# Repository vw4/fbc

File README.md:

# Footwell Backlight Controller

- Independent two-channel control with smooth fade transitions
- Delayed switch-off feature (can be disabled via T58b input)
- Low power standby mode

### FSM Diagram

## Schematics

## Partlist

### PCB

There are known issues with PCB layout

- The distance between the 4-pin connectors and the mounting holes is shorter by 0.5mm.
- All connectors need to be moved outward by 3.6mm to match the case outline.
- There are errors in the positions of the J1 and J2 labels on the silkscreen; the labels are placed on the solder pads.
- D1 is too close to the J3 connector housing.

| Qty | Value        | Device        | Package          | Parts                            | Description                                             | MF MPN        | OC_FARNELL | OC_NEWARK | PACKAGE  | SUPPLIER        |
|-----|--------------|---------------|------------------|----------------------------------|---------------------------------------------------------|---------------|------------|-----------|----------|-----------------|
| 2   | 100n         | Capacitor     | C025-025X050     | C1, C3                           | ceramic or polyester capacitor                          |               |            |           |          |                 |
| 2   | 100uF 20V    | Capacitor     | E3,5-8           | C2, C4                           | electrolytic capacitor                                  |               |            |           |          |                 |
| 8   | 10k          | Resistor      | 0207/10          | R1, R2, R3, R5, R8, R9, R12, R13 | 1/4 Watt, ±5%                                           |               |            |           |          |                 |
| 1   | 1N4004       | 1N4004        | DO41-10          | D1                               | DIODE                                                   |               |            |           |          |                 |
| 2   | 1N4148       | 1N4148        | DO35-10          | D2, D3                           | DIODE                                                   |               |            |           |          |                 |
| 3   | 1k           | Resistor      | 0207/10          | R4, R10, R11                     | 1/4 Watt, ±5%                                           |               |            |           |          |                 |
| 2   | 2.2k         | Resistor      | 0207/10          | R6, R7                           | 1/4 Watt, ±5%                                           |               |            |           |          |                 |
| 2   | 5-104935-6   | Connector     | 7395-04          | J1, J2                           | CONNECTOR - LATCHING HDR SHRD 5P W/O HOLD-DN 30AU CNT   | 5-104935-6    |            |           |          | TE Connectivity |
| 1   | 5-104935-6   | Connector     | 7395-05          | J3                               | CONNECTOR - LATCHING HDR SHRD 4P W/O HOLD-DN 30AU CNT   | 5-104935-1    |            |           |          | TE Connectivity |
| 1   | 4N25M        | 4N25M         | DIL06            | OK1                              | General Purpose 6-Pin Phototransistor Optocouplers      | 4N25-M        | 1021349    | 98K9084   |          |                 |
| 1   | 78L05Z       | 78L05Z        | TO92             | IC1                              | Positive VOLTAGE REGULATOR                              |               |            |           |          |                 |
| 1   | ATTINY85     | ATTINY85-20PU | DIP254P762X533-8 | U1                               | 8-bit Microcontroller with In-System Programmable Flash | ATTINY85-20PU | 1455162    | 58M3796   | PDIP-8   | Atmel           |
| 2   | BC327        | BC32725TA     | TO92-EBC         | T3, T4                           | PNP Transistor                                          |               |            |           |          |                 |
| 2   | BC547        | BC547CTA      | TO92-CBE         | T1, T2                           | NPN Transistor                                          |               |            |           |          |                 |

### Wiring

| Qty | Mfr.            | Mfr. No. | Description         |
|-----|-----------------|----------|---------------------|
| 2   | TE Connectivity | 104257-3 | RECEPTACLE ASSY 4P  |
| 1   | TE Connectivity | 104257-4 | RECEPTACLE ASSY 5P  |
| 13  | TE Connectivity | 104479-3 | CONTACT SHORT 24-20 |
| -   |                 |          | 20 AWG wire         |

### Enclosure

M3 threads need to be tapped in the bottom part. Assembly requires M3x20mm bolts.

| Printing method | Material | Color | Layer height | Infill |
|-----------------|----------|-------|--------------|--------|
| FDM             | ABS      | Black | 0.1 mm       | 40%    |

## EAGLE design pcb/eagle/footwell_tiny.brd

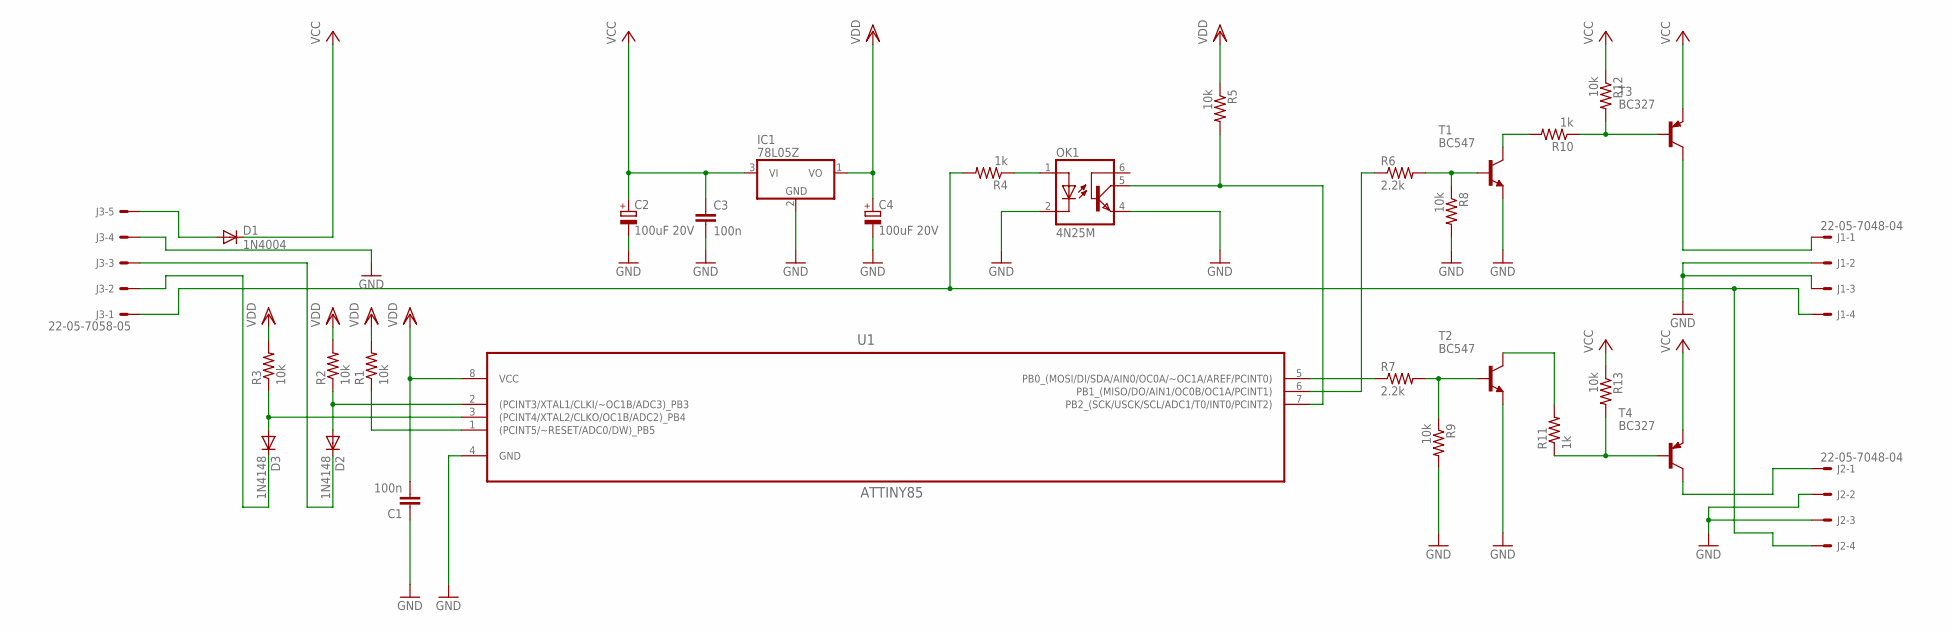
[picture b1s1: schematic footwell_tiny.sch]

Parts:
C1, C3: 100n; C025-025X050
C2, C4: 100uF 20V; E3,5-8
D1: 1N4004; DO41-10
D2, D3: 1N4148; DO35-10
IC1: 78L05Z; TO92
J1, J2: 22-05-7048-04; 7395-04
J3: 22-05-7058-05; 7395-05
OK1: 4N25M; DIL06
R1, R2, R3, R5, R8, R9, R12, R13: 10k; 0207/10
R4, R10, R11: 1k; 0207/10
R6, R7: 2.2k; 0207/10
T1, T2: BC547; TO92-CBE
T3, T4: BC327; TO92-EBC
U1: ATTINY85; DIP254P762X533-8

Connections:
DOOR0: D2.C, J3.3
DOOR1: D3.C, J3.2
GND: C1.1, C2.-, C3.2, C4.-, IC1.2 (GND), J1.2, J1.3, J2.2, J2.3, J3.4, OK1.2 (C), OK1.4 (EMI), R8.2, R9.2, T1.E, T2.E, U1.4 (GND)
unnamed: R1.1, U1.1 ((PCINT5/~RESET/ADC0/DW)_PB5)
unnamed: R10.1, R12.2, T3.B
unnamed: R10.2, T1.C
unnamed: R6.2, R8.1, T1.B
unnamed: R11.1, R13.2, T4.B
unnamed: R11.2, T2.C
unnamed: R7.2, R9.1, T2.B
unnamed: R6.1, U1.6 (PB1_(MISO/DO/AIN1/OC0B/OC1A/PCINT1))
unnamed: R7.1, U1.5 (PB0_(MOSI/DI/SDA/AIN0/OC0A/~OC1A/AREF/P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)
unnamed: OK1.1 (A), R4.1
unnamed: OK1.5 (COL), R5.2, U1.7 (PB2_(SCK/USCK/SCL/ADC1/T0/INT0/PCINT2))
unnamed: J1.4, J2.4, J3.1, R4.2
unnamed: J2.1, T4.C
unnamed: J1.1, T3.C
unnamed: D1.A, J3.5
PB3: D2.A, R2.1, U1.2 ((PCINT3/XTAL1/CLKI/~OC1B/ADC3)_PB3)
PB4: D3.A, R3.1, U1.3 ((PCINT4/XTAL2/CLKO/OC1B/ADC2)_PB4)
VCC: C2.+, C3.1, D1.C, IC1.3 (VI), R12.1, R13.1, T3.E, T4.E
VDD: C1.2, C4.+, IC1.1 (VO), R1.2, R2.2, R3.2, R5.1, U1.8 (VCC)

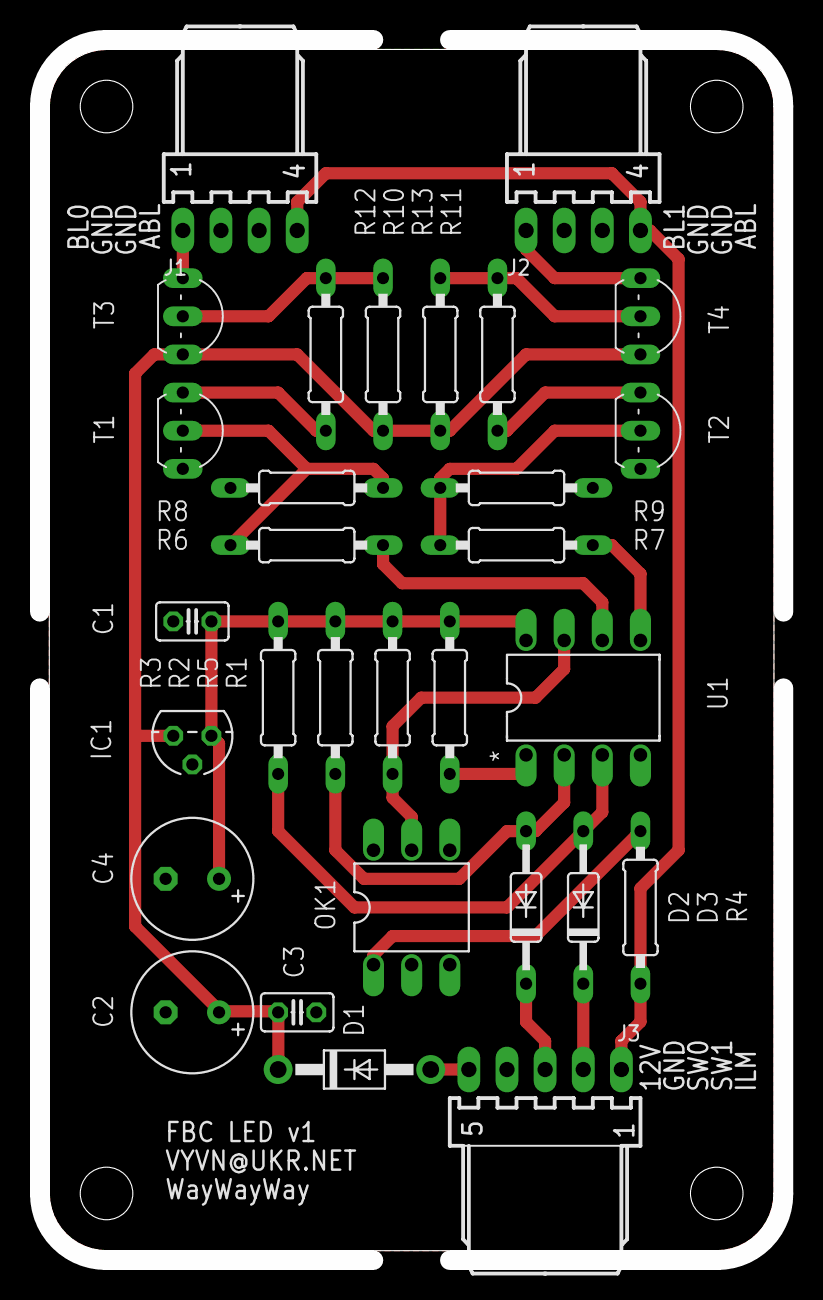
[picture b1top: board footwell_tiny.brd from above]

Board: 2 copper layers, 49.5 x 81.3 mm, 30 parts (0 on the bottom side), 22 nets.

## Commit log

2024-09-18 readme fixed
2024-09-18 STL added
2025-12-30 Firmware refactored - removed arduino dependency and cmake added - added pwm gamma correction - FSM refactored - race conditions fixed
2025-12-31 add avrdude targets
